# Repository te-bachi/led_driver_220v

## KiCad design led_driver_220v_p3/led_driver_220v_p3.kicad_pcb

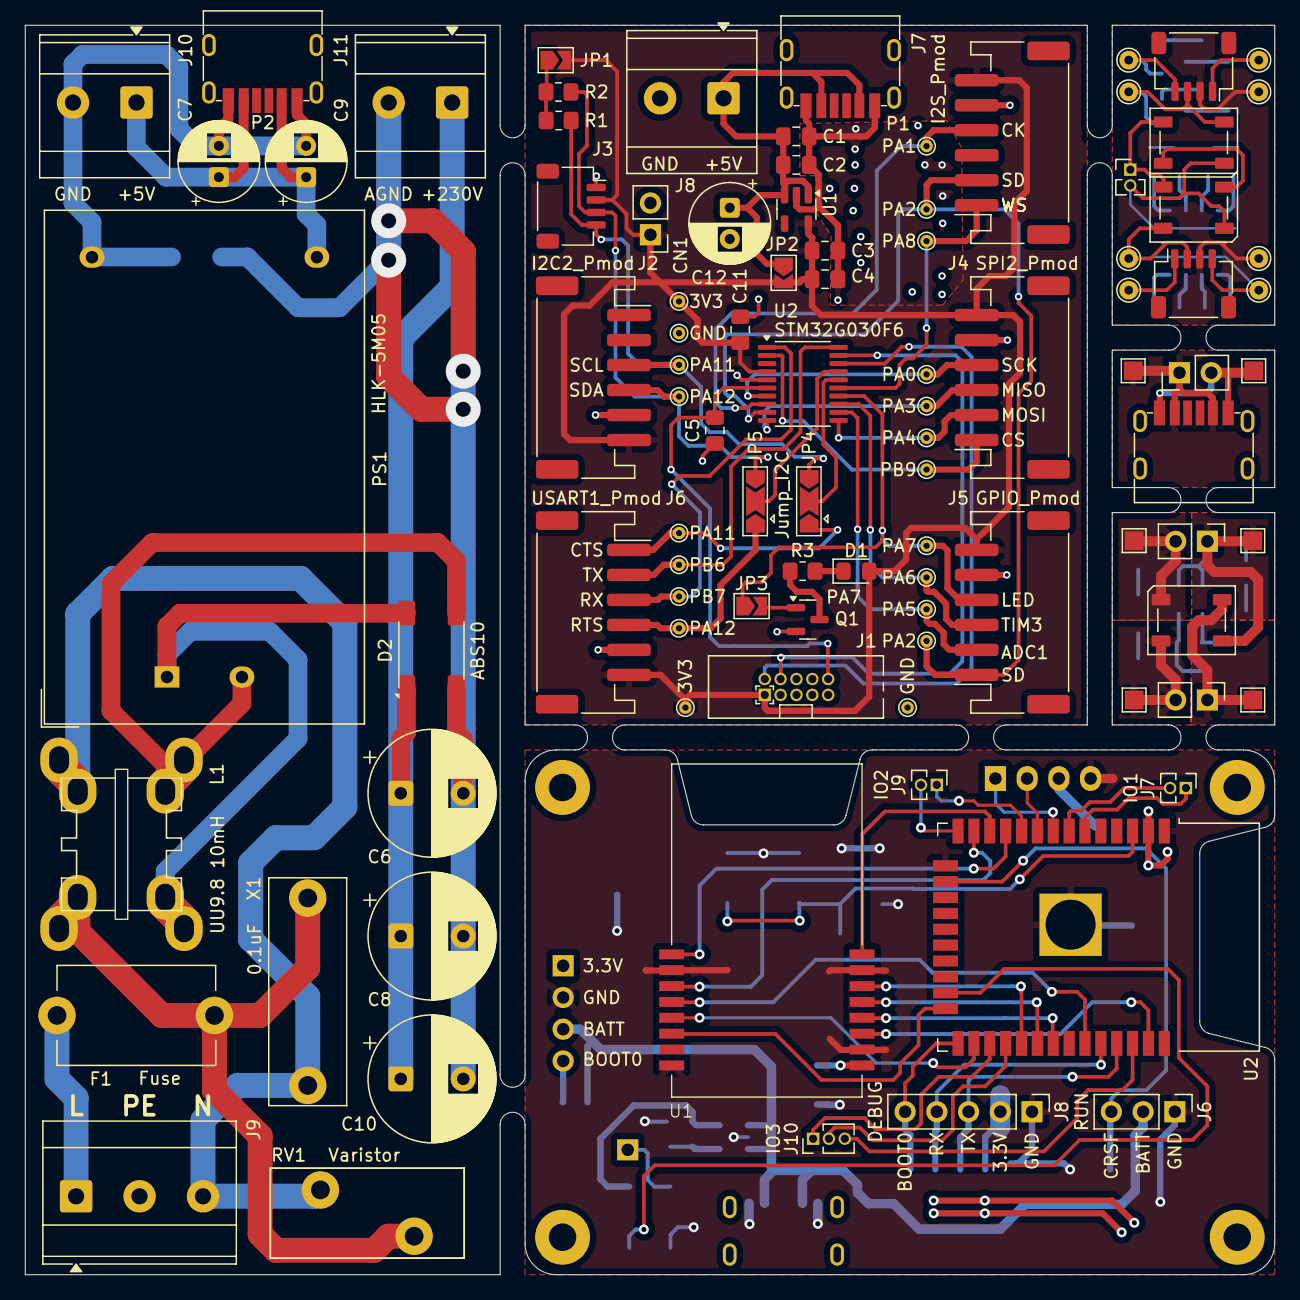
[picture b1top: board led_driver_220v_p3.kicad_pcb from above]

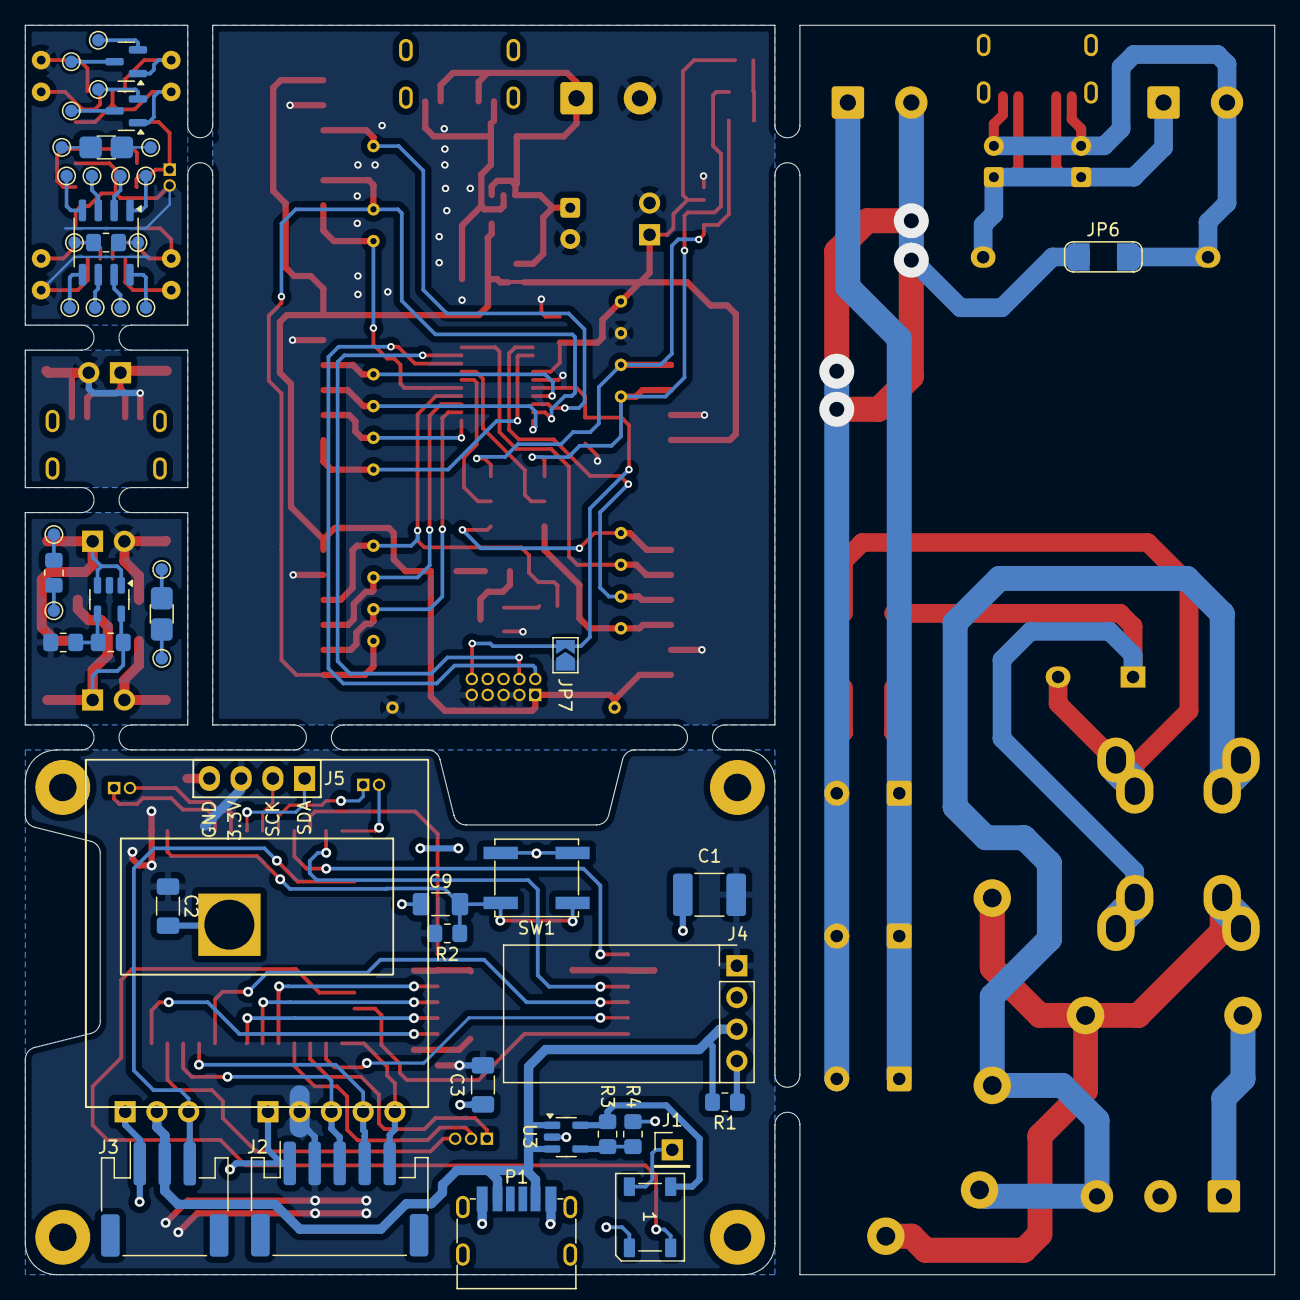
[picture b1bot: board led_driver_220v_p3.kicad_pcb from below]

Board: 2 copper layers, 100.0 x 100.0 mm, 149 parts (49 on the bottom side), 98 nets.

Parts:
C1, C4: 10uF; C_0805_2012Metric_Pad1.18x1.45mm_HandSolder
C1#2: 10uF; C_1812_4532Metric_Pad1.57x3.40mm_HandSolder
C2, C3, C5, C11: 100nF; C_0805_2012Metric_Pad1.18x1.45mm_HandSolder
C2#2, C3#2, C9#2: 10uF; C_1206_3216Metric_Pad1.33x1.80mm_HandSolder
C6, C8, C10: 6.8uF; CP_Radial_D10.0mm_P5.00mm
C7, C9, C12: 220uF; CP_Radial_D6.3mm_P2.50mm
CN1: 3.3V; PinHeader_1x02_P2.54mm_Vertical
D1: LED; LED_0805_2012Metric_Pad1.15x1.40mm_HandSolder
D1#2, D3, D4, D5: WS2812B; LED_WS2812B_PLCC4_5.0x5.0mm_P3.2mm
D2: ABS10; Diode_Bridge_Diotec_ABS
F1: Fuse; Fuse_Cylinder_3.6x10mm_Horizontal
H1, H2, H3, H4: MountingHole; MountingHole_2.2mm_M2_Pad
J1: SWD; SWD_2x05_P1.27mm
J1#2: LED Chain; PinHeader_1x01_P2.54mm_Vertical
J2: I2C2_Pmod; JST_PH_S6B-PH-SM4-TB_1x06-1MP_P2.00mm_Horizontal
J2#2: DEBUG; JST_PH_S5B-PH-SM4-TB_1x05-1MP_P2.00mm_Horizontal
J3: I2C2_Qwiic; JST_SH_SM04B-SRSS-TB_1x04-1MP_P1.00mm_Horizontal
J3#2: RUN; JST_PH_S3B-PH-SM4-TB_1x03-1MP_P2.00mm_Horizontal
J4: SPI2_Pmod; JST_PH_S6B-PH-SM4-TB_1x06-1MP_P2.00mm_Horizontal
J4#2: DC_DC; DC_DC_20x11
J5: GPIO_Pmod; JST_PH_S6B-PH-SM4-TB_1x06-1MP_P2.00mm_Horizontal
J5#2: OLED_I2C; OLED_27.3x27.8mm_no_holes
J6: USART1_Pmod; JST_PH_S6B-PH-SM4-TB_1x06-1MP_P2.00mm_Horizontal
J6#2: RUN; PinHeader_1x03_P2.54mm_Vertical
J7: I2S_Pmod; JST_PH_S6B-PH-SM4-TB_1x06-1MP_P2.00mm_Horizontal
J7#2: IO1; PinHeader_1x02_P1.27mm_Vertical
J8: Input_5V; TerminalBlock_Phoenix_MKDS-3-2-5.08_1x02_P5.08mm_Horizontal
J8#2: DEBUG; PinHeader_1x05_P2.54mm_Vertical
J9: AC-Input-230V; TerminalBlock_Phoenix_MKDS-3-3-5.08_1x03_P5.08mm_Horizontal
J9#2: IO2; PinHeader_1x02_P1.27mm_Vertical
J10: IO3; PinHeader_1x03_P1.27mm_Vertical
J10#2: DC-Output-5V; TerminalBlock_Phoenix_MKDS-3-2-5.08_1x02_P5.08mm_Horizontal
J11: DC-Output-230V; TerminalBlock_Phoenix_MKDS-3-2-5.08_1x02_P5.08mm_Horizontal
J12, J14: V; PinHeader_1x02_P2.54mm_Vertical
J13: D; PinHeader_1x02_P2.54mm_Vertical
J15: Qwiic_IN; JST_SH_SM04B-SRSS-TB_1x04-1MP_P1.00mm_Horizontal
J16: Qwiic_Out; JST_SH_SM04B-SRSS-TB_1x04-1MP_P1.00mm_Horizontal
J17: 5.0V; PinHeader_1x02_P1.27mm_Vertical
J51: SOIC-8; SO-8_3.9x4.9mm_P1.27mm
JP1: Jump_I2C2; SolderJumper-2_P1.3mm_Open_TrianglePad1.0x1.5mm
JP2: Jump_LDO; SolderJumper-2_P1.3mm_Open_TrianglePad1.0x1.5mm
JP3: Jump_LED; SolderJumper-2_P1.3mm_Open_TrianglePad1.0x1.5mm
JP4, JP5: Jump_I2C; SolderJumper-3_P2.0mm_Open_TrianglePad1.0x1.5mm
JP6: Jump-; SolderJumper-2
JP7: Jump_NRST; SolderJumper-2_P1.3mm_Open_TrianglePad1.0x1.5mm
L1: UU9.8 10mH; L_CommonMode_UU9.8_UU10.5
P1, P1#2, P2, P3: USB_C_Plug_USB2.0; USB_C_DEALON_009
PS1: HLK-5M05; Converter_ACDC_Hi-Link_HLK-5Mxx
Q1, Q2, Q3: BSS138; SOT-23
R1, R2: 2.2k; R_0805_2012Metric_Pad1.20x1.40mm_HandSolder
R1#2, R2#2: 10k; R_0805_2012Metric_Pad1.20x1.40mm_HandSolder
R3, R5, R9: R; R_0805_2012Metric_Pad1.20x1.40mm_HandSolder
R3#2, R6: 56k; R_0805_2012Metric_Pad1.20x1.40mm_HandSolder
R4, R7: 22k; R_0805_2012Metric_Pad1.20x1.40mm_HandSolder
R4#2, R8: R; R_1206_3216Metric_Pad1.30x1.75mm_HandSolder
RV1: Varistor; RV_Disc_D15.5mm_W7.2mm_P7.5mm
SW1: RESET; SW_SPST_EVQP0
TP1: PA0; TestPoint_THTPad_D1.0mm_Drill0.5mm_narrow
TP2: PA1; TestPoint_THTPad_D1.0mm_Drill0.5mm_narrow
TP3: PA3; TestPoint_THTPad_D1.0mm_Drill0.5mm_narrow
TP3a1, TP3b1: PA2; TestPoint_THTPad_D1.0mm_Drill0.5mm_narrow
TP4: PA4; TestPoint_THTPad_D1.0mm_Drill0.5mm_narrow
TP5: PA5; TestPoint_THTPad_D1.0mm_Drill0.5mm_narrow
TP6: PA6; TestPoint_THTPad_D1.0mm_Drill0.5mm_narrow
TP7: PA7; TestPoint_THTPad_D1.0mm_Drill0.5mm_narrow
TP8: PA8; TestPoint_THTPad_D1.0mm_Drill0.5mm_narrow
TP9: PB6; TestPoint_THTPad_D1.0mm_Drill0.5mm_narrow
TP9a1, TP9b1: PA11; TestPoint_THTPad_D1.0mm_Drill0.5mm_narrow
TP10: PB7; TestPoint_THTPad_D1.0mm_Drill0.5mm_narrow
TP10a1, TP10b1: PA12; TestPoint_THTPad_D1.0mm_Drill0.5mm_narrow
TP11: PB9; TestPoint_THTPad_D1.0mm_Drill0.5mm_narrow
TP12, TP13: 3V3; TestPoint_THTPad_D1.0mm_Drill0.5mm_narrow
TP14, TP15: GND; TestPoint_THTPad_D1.0mm_Drill0.5mm_narrow
TP16, TP18, TP20: USB+5V; TestPoint_Pad_1.5x1.5mm
TP17, TP19, TP21: USB-GND; TestPoint_Pad_1.5x1.5mm
TP22, TP23, TP24, TP25, TP26, TP27, TP28, TP29: TestPoint_THTPad_D1.5mm_Drill0.7mm
TP30, TP31, TP32, TP33, TP34, TP35, TP36, TP37, TP38, TP39, TP40, TP41, TP42, TP43, TP44, TP45, TP46, TP47, TP48, TP49: TestPoint_Pad_D1.0mm
U1: E28-2G4M27S-MY; E28-2G4M27S
U1#2: TLV75533PDBV; SOT-23-5
U2: STM32G030F6; TSSOP-20_4.4x6.5mm_P0.65mm
U2#2: ESP32-WROOM-32-MY; ESP32-WROOM-32_zhaw
U3, U3#2: SPX3819M5-L; SOT-23-5
X1: 0.1uF; C_Rect_L18.0mm_W6.0mm_P15.00mm_FKS3_FKP3

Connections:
+3.3V: C1#2.1, C2#2.1, C3.2, C3#2.1, C4.2, C11.2, CN1.1, D1.2 (A), J1.1, J2.6, J2#2.2, J3.2, J4.6, J4#2.1, J5.6, J5#2.2, J6.6, J7.6, J8#2.2, JP1.2 (B), JP2.2 (B), R2#2.2, TP12.1, TP13.1, U1.1 (VCC), U1#2.5 (OUT), U2.4 (VDD/VDDA), U2#2.2 (VDD)
+5V: C1.2, C2.2, C12.1, D1#2.1 (VDD), D3.1 (VDD), J8.1, J14.1, JP2.1 (A), P1.A9 (VBUS), P1.B9 (VBUS), R3#2.1, TP18.1, U1#2.1 (IN), U1#2.3 (EN), U3.1 (IN), U3.3 (EN), U3#2.5 (OUT)
+BATT: J3#2.2, J4#2.3, J6#2.2, P1#2.A9 (VBUS), P1#2.B9 (VBUS), R1#2.2, U3#2.1 (IN), U3#2.3 (EN)
/Addition/IN: D3.4 (DIN), J13.2, TP21.1
/Addition/OUT: D3.2 (DOUT), J13.1, R6.1, TP20.1, U3.5 (OUT)
/Addition/Q_3.3V: J15.2, J16.3, TP24.1, TP28.1
/Addition/Q_5.0V: D4.1 (VDD), D5.1 (VDD), J17.1
/Addition/Q_GND: D4.3 (VSS), D5.3 (VSS), J15.1, J16.4, J17.2, TP25.1, TP29.1
/Addition/Q_SCL_IN: J15.4, Q2.1 (G), TP22.1
/Addition/Q_SCL_OUT: J16.1, TP26.1
/Addition/Q_SDA_IN: D4.4 (DIN), J15.3, Q3.1 (G), TP23.1
/Addition/Q_SDA_OUT: D5.2 (DOUT), J16.2, TP27.1
/Addition/USB+5V: J12.1, P3.A9 (VBUS), P3.B9 (VBUS), TP16.1
/Addition/USB-GND: J12.2, P3.A12 (GND), P3.B12 (GND), TP17.1
/CRSF_RX_TX: J3#2.3, J6#2.3, U2#2.16 (IO13)
/E28_BUSY: U1.12 (BUSY), U2#2.33 (IO21)
/E28_DIO1: U1.13 (DIO1), U2#2.26 (IO4)
/E28_DIO2: U1.14 (DIO2), U2#2.24 (IO2)
/E28_MISO_RX: U1.4 (MOSI_RX), U2#2.31 (IO19)
/E28_MISO_TX: U1.3 (MISO_TX), U2#2.37 (IO23)
/E28_NRESET: U1.11 (NRESET), U2#2.13 (IO14)
/E28_NSS_CTS: U1.6 (NSS_CTS), U2#2.29 (IO5)
/E28_RX_EN: U1.8 (RX_EN), U2#2.12 (IO27)
/E28_SCK_RTS: U1.5 (SCK_RTS), U2#2.30 (IO18)
/E28_TX_EN: U1.9 (TX_EN), U2#2.11 (IO26)
/EN: C9#2.1, R2#2.1, SW1.2, U2#2.3 (EN)
/ESP32_BOOT0: J2#2.5, J8#2.5, U2#2.25 (IO0)
/ESP32_RX: J2#2.4, J8#2.4, U2#2.34 (RXD0/IO3)
/ESP32_TX: J2#2.3, J8#2.3, U2#2.35 (TXD0/IO1)
/High Voltage/DC+5V: C7.1, C9.1, J10#2.1, P2.A9 (VBUS), P2.B9 (VBUS), PS1.4 (+Vout)
/High Voltage/DC+230V: C6.1, C8.1, C10.1, D2.1 (+), J11.1
/High Voltage/DC-AGND: C6.2, C8.2, C10.2, D2.2 (-), J11.2, JP6.1 (A)
/High Voltage/DC-GND: C7.2, C9.2, J10#2.2, JP6.2 (B), P2.A12 (GND), P2.B12 (GND), PS1.3 (-Vout)
/High Voltage/L: F1.1, J9.1
/High Voltage/N: J9.3, L1.3, RV1.2, X1.2
/High Voltage/TIN_L: F1.2, L1.1, RV1.1, X1.1
/High Voltage/TOUT_L: D2.4, L1.2, PS1.1 (AC/L)
/High Voltage/TOUT_N: D2.3, L1.4, PS1.2 (AC/N)
/IO12: J9#2.2, U2#2.14 (IO12)
/IO16: J10.1, U2#2.27 (IO16)
/IO17: J10.2, U2#2.28 (IO17)
/IO22: J10.3, U2#2.36 (IO22)
/IO25: J9#2.1, U2#2.10 (IO25)
/IO34: J7#2.1, U2#2.6 (IO34)
/IO35: J7#2.2, U2#2.7 (IO35)
/LED_RGB: D1#2.4 (DIN), U2#2.23 (IO15)
/MCU/FETD: Q1.3 (D), R3.1
/MCU/FETG: JP3.2 (B), Q1.1 (G)
/MCU/GPIO_ADC1_IN5: J5.2, TP5.1, U2.12 (PA5)
/MCU/GPIO_PA7: J5.4, JP3.1 (A), TP7.1, U2.14 (PA7)
/MCU/GPIO_TIM3_CH1: J5.3, TP6.1, U2.13 (PA6)
/MCU/I2C2_SCL: J2.3, J3.4, JP4.3 (B), R1.2, TP9a1.1
/MCU/I2C2_SCL_UART1_CTS: JP4.2 (C), U2.16 (PA11_[PA9])
/MCU/I2C2_SDA: J2.4, J3.3, JP5.3 (B), R2.2, TP10a1.1
/MCU/I2C2_SDA_UART1_RTS: JP5.2 (C), U2.17 (PA12_[PA10])
/MCU/I2S1_CK: J7.4, TP2.1, U2.8 (PA1)
/MCU/I2S1_SD: J5.1, J7.2, TP3a1.1, TP3b1.1, U2.9 (PA2)
/MCU/I2S1_WS: J7.1, TP8.1, U2.15 (PB0/PB1/PB2/PA8)
/MCU/LED: D1.1 (K), R3.2
/MCU/NRST: C5.2, J1.10, JP7.2 (B), U2.6 (~RST/PF2)
/MCU/SPI2_CS: J4.1, TP11.1, U2.2 (PB9/PC14-OSC32_IN)
/MCU/SPI2_MISO: J4.3, TP3.1, U2.10 (PA3)
/MCU/SPI2_MOSI: J4.2, TP4.1, U2.11 (PA4)
/MCU/SPI2_SCK: J4.4, TP1.1, U2.7 (PA0)
/MCU/SWCLK: J1.4, U2.19 (PA15/PA14-BOOT0)
/MCU/SWDIO: J1.2, U2.18 (PA13)
/MCU/USART1_CTS: J6.1, JP4.1 (A), TP9b1.1
/MCU/USART1_RTS: J6.4, JP5.1 (A), TP10b1.1
/MCU/USART1_RX: J6.3, TP10.1, U2.1 (PB7/PB8)
/MCU/USART1_TX: J6.2, TP9.1, U2.20 (PB3/PB4/PB5/PB6)
/OLED_SCK: J5#2.3, U2#2.9 (IO33)
/OLED_SDA: J5#2.4, U2#2.8 (IO32)
GND: C1.1, C1#2.2, C2.1, C2#2.2, C3.1, C3#2.2, C4.1, C5.1, C9#2.2, C11.1, C12.2, CN1.2, D1#2.3 (VSS), D3.3 (VSS), J1.3, J1.5, J1.9, J2.5, J2#2.1, J3.1, J3#2.1, J4.5, J4#2.2, J5.5, J5#2.1, J6.5, J6#2.1, J7.5, J8.2, J8#2.1, J14.2, JP7.1 (A), P1.A12 (GND), P1.B12 (GND), P1#2.A12 (GND), P1#2.B12 (GND), Q1.2 (S), R4.2, R7.2, SW1.1, TP14.1, TP15.1, TP19.1, U1.2 (GND), U1.7 (GND), U1.10 (GND), U1.16 (GND), U1#2.2 (GND), U2.5 (VSS/VSSA), U2#2.1 (GND), U2#2.15 (GND), U2#2.38 (GND), U2#2.39 (GND), U3.2 (GND), U3#2.2 (GND)
unnamed: D1#2.2 (DOUT), J1#2.1
unnamed: D4.2 (DOUT), D5.4 (DIN)
unnamed: J4#2.4, R1#2.1
unnamed: J51.1, TP37.1
unnamed: J51.2, TP36.1
unnamed: J51.3, TP35.1
unnamed: J51.4, TP34.1
unnamed: J51.5, TP38.1
unnamed: J51.6, TP39.1
unnamed: J51.7, TP40.1
unnamed: J51.8, TP41.1
unnamed: JP1.1 (A), R1.1, R2.1
unnamed: Q2.3 (D), TP30.1
unnamed: Q2.2 (S), TP33.1
unnamed: Q3.3 (D), TP31.1
unnamed: Q3.2 (S), TP32.1
unnamed: R4#2.1, TP42.1
unnamed: R4#2.2, TP43.1
unnamed: R5.1, TP44.1
unnamed: R5.2, TP45.1
unnamed: R8.1, TP46.1
unnamed: R8.2, TP48.1
unnamed: R9.1, TP47.1
unnamed: R9.2, TP49.1
unnamed: R3#2.2, R4.1, R6.2, R7.1, U3.4 (ADJ), U3#2.4 (ADJ)

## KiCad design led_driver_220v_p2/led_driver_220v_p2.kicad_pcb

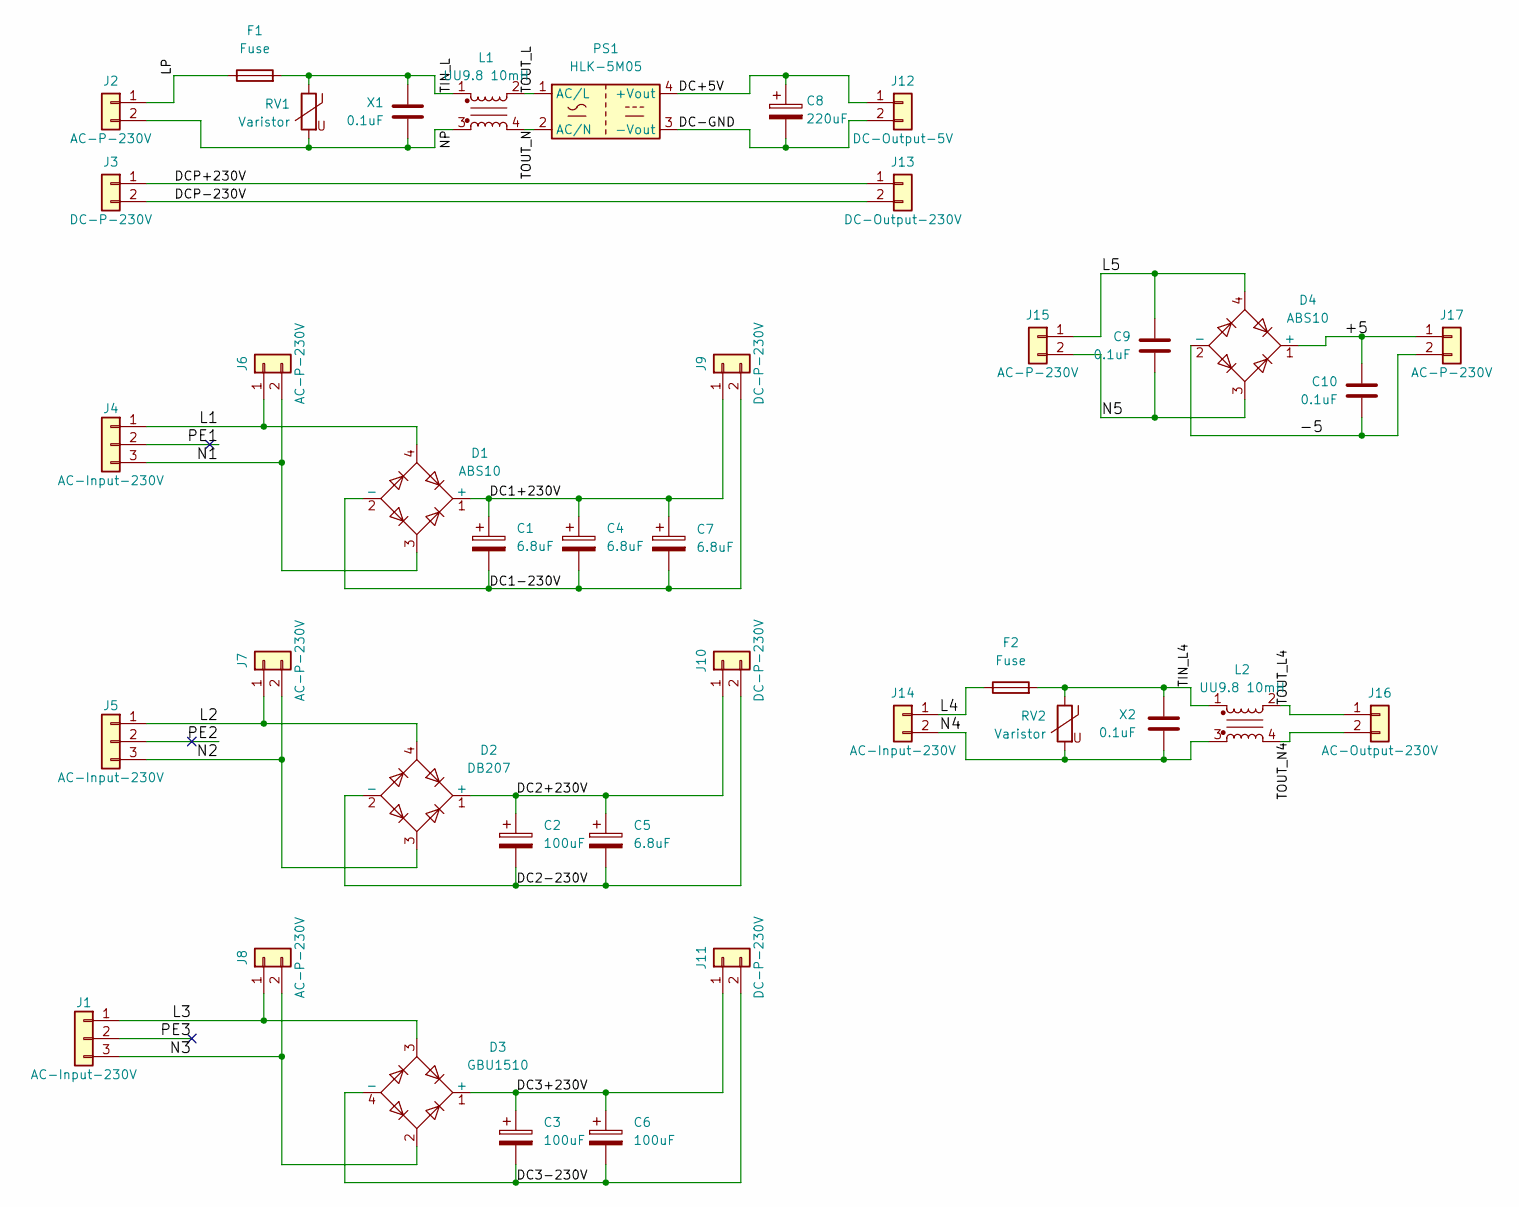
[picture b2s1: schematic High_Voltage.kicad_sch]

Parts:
C1, C4, C5, C7: 6.8uF; CP_Radial_D10.0mm_P5.00mm
C2, C3, C6: 100uF; CP_Radial_D18.0mm_P7.50mm
C8: 220uF; CP_Radial_D10.0mm_P5.00mm
C9, C10: 0.1uF; C_1812_4532Metric_Pad1.57x3.40mm_HandSolder
D1, D4: ABS10; Diode_Bridge_Diotec_ABS
D2: DB207; Diode_Bridge_DIP-4_W7.62mm_P5.08mm
D3: GBU1510; Diode_Bridge_Vishay_GBU
F1, F2: Fuse; Fuse_Cylinder_3.6x10mm_Horizontal
J1, J4, J5: AC-Input-230V; TerminalBlock_Phoenix_MKDS-3-3-5.08_1x03_P5.08mm_Horizontal
J2, J6, J7, J8, J15, J17: AC-P-230V; TerminalBlock_P5.08mm_Horizontal
J3, J9, J10, J11: DC-P-230V; TerminalBlock_P5.08mm_Horizontal
J12: DC-Output-5V; TerminalBlock_Phoenix_MKDS-3-2-5.08_1x02_P5.08mm_Horizontal
J13: DC-Output-230V; TerminalBlock_Phoenix_MKDS-3-2-5.08_1x02_P5.08mm_Horizontal
J14: AC-Input-230V; TerminalBlock_Phoenix_MKDS-3-2-5.08_1x02_P5.08mm_Horizontal
J16: AC-Output-230V; TerminalBlock_Phoenix_MKDS-3-2-5.08_1x02_P5.08mm_Horizontal
L1, L2: UU9.8 10mH; L_CommonMode_UU9.8_UU10.5
PS1: HLK-5M05; Converter_ACDC_Hi-Link_HLK-5Mxx
RV1, RV2: Varistor; RV_Disc_D15.5mm_W7.2mm_P7.5mm
X1, X2: 0.1uF; C_Rect_L18.0mm_W6.0mm_P15.00mm_FKS3_FKP3

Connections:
/High Voltage/+5: C10.1, D4.1 (+), J17.1
/High Voltage/-5: C10.2, D4.2 (-), J17.2
/High Voltage/DC1+230V: C1.1, C4.1, C7.1, D1.1 (+), J9.1
/High Voltage/DC1-230V: C1.2, C4.2, C7.2, D1.2 (-), J9.2
/High Voltage/DC2+230V: C2.1, C5.1, D2.1 (+), J10.1
/High Voltage/DC2-230V: C2.2, C5.2, D2.2 (-), J10.2
/High Voltage/DC3+230V: C3.1, C6.1, D3.1 (+), J11.1
/High Voltage/DC3-230V: C3.2, C6.2, D3.4 (-), J11.2
/High Voltage/DC+5V: C8.1, J12.1, PS1.4 (+Vout)
/High Voltage/DC-GND: C8.2, J12.2, PS1.3 (-Vout)
/High Voltage/DCP+230V: J3.1, J13.1
/High Voltage/DCP-230V: J3.2, J13.2
/High Voltage/L1: D1.4, J4.1, J6.1
/High Voltage/L2: D2.4, J5.1, J7.1
/High Voltage/L3: D3.3, J1.1, J8.1
/High Voltage/L4: F2.1, J14.1
/High Voltage/L5: C9.1, D4.4, J15.1
/High Voltage/LP: F1.1, J2.1
/High Voltage/N1: D1.3, J4.3, J6.2
/High Voltage/N2: D2.3, J5.3, J7.2
/High Voltage/N3: D3.2, J1.3, J8.2
/High Voltage/N4: J14.2, L2.3, RV2.2, X2.2
/High Voltage/N5: C9.2, D4.3, J15.2
/High Voltage/NP: J2.2, L1.3, RV1.2, X1.2
/High Voltage/PE1: J4.2
/High Voltage/PE2: J5.2
/High Voltage/PE3: J1.2
/High Voltage/TIN_L: F1.2, L1.1, RV1.1, X1.1
/High Voltage/TIN_L4: F2.2, L2.1, RV2.1, X2.1
/High Voltage/TOUT_L: L1.2, PS1.1 (AC/L)
/High Voltage/TOUT_L4: J16.1, L2.2
/High Voltage/TOUT_N: L1.4, PS1.2 (AC/N)
/High Voltage/TOUT_N4: J16.2, L2.4

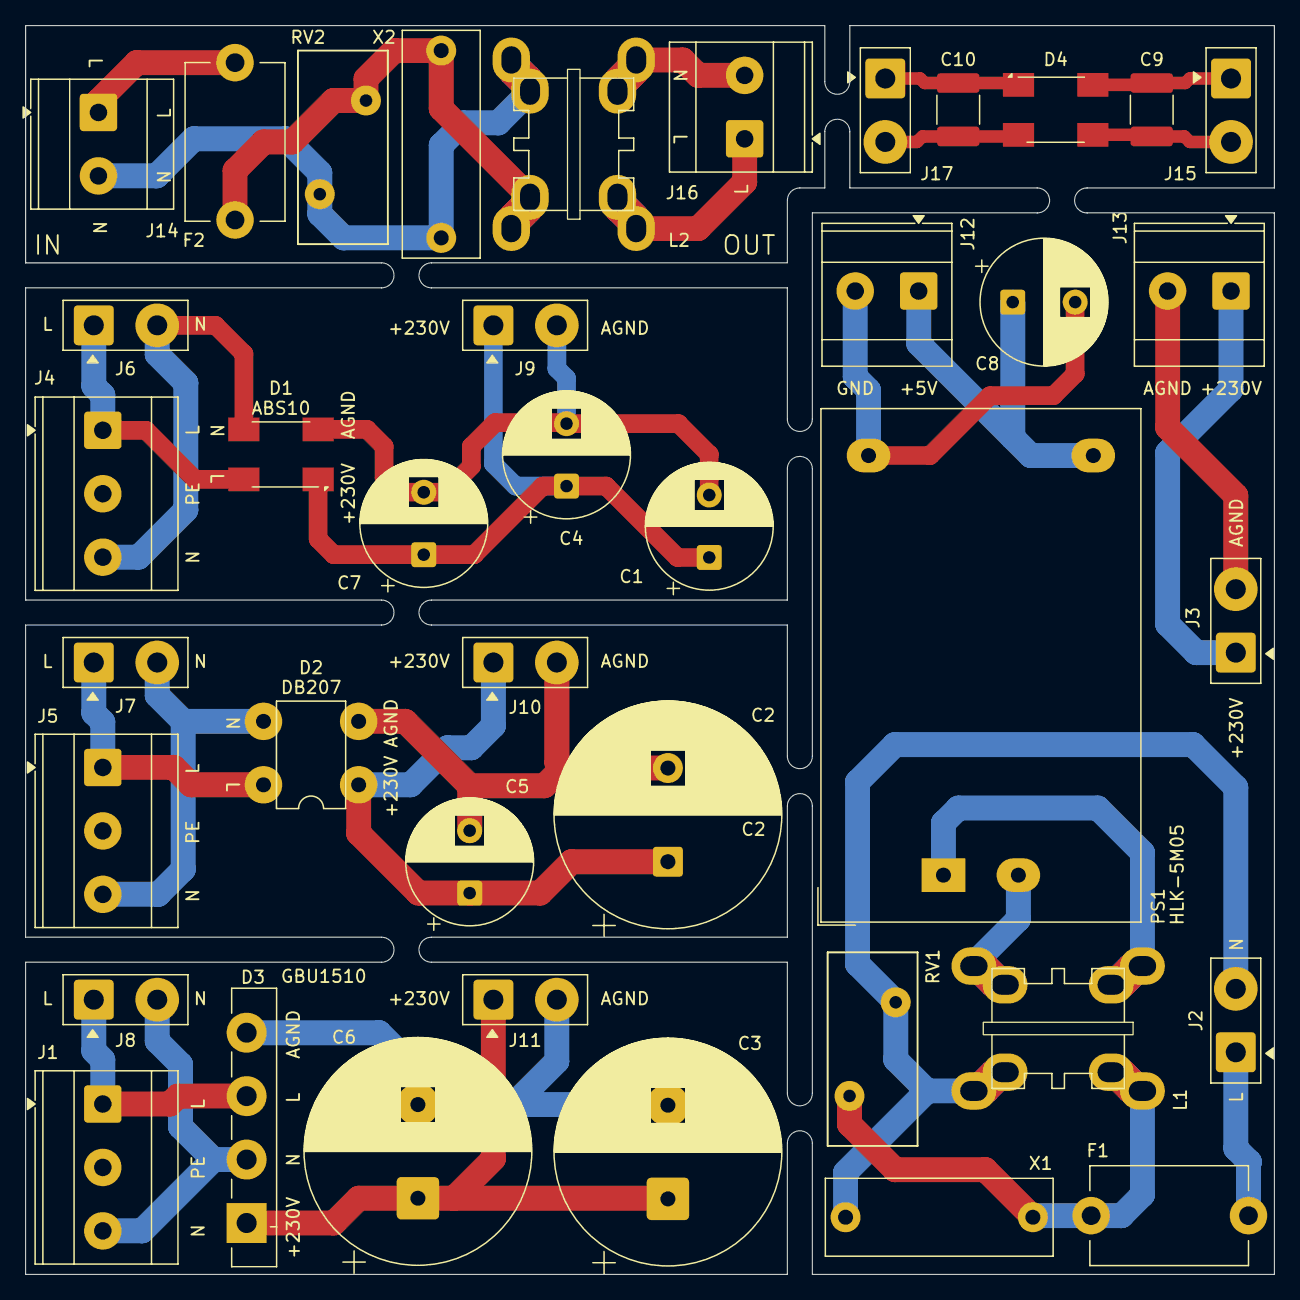
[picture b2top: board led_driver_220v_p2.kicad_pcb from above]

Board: 2 copper layers, 100.0 x 100.0 mm, 40 parts (0 on the bottom side), 30 nets.

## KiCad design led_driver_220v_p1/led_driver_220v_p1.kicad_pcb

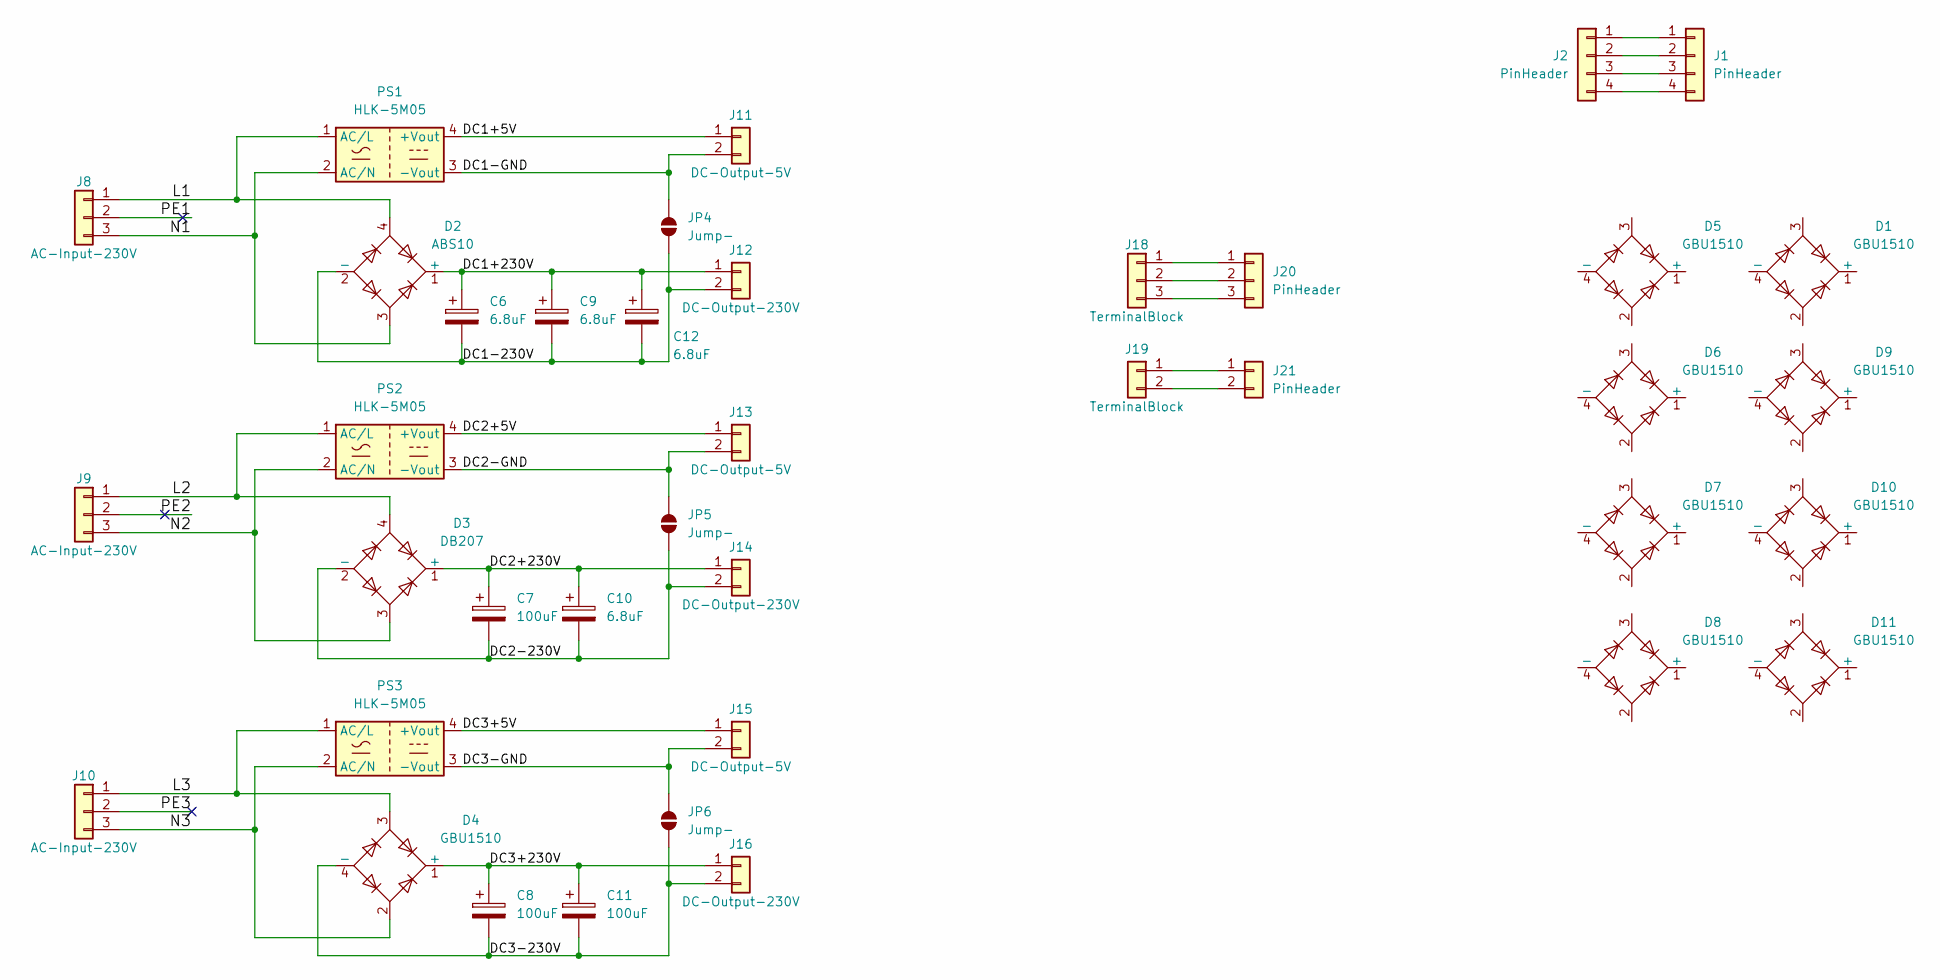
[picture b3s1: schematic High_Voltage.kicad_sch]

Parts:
C6, C9, C10, C12: 6.8uF; CP_Radial_D10.0mm_P5.00mm
C7, C8, C11: 100uF; CP_Radial_D18.0mm_P7.50mm
D1, D4, D5, D6, D7, D8, D9, D10, D11: GBU1510; Diode_Bridge_Vishay_GBU
D2: ABS10; Diode_Bridge_Diotec_ABS
D3: DB207; Diode_Bridge_DIP-4_W7.62mm_P5.08mm
J1: PinHeader; Diode_Bridge_Vishay_GBU
J2: PinHeader; PinHeader_1x04_P2.54mm_Vertical
J8, J9, J10: AC-Input-230V; TerminalBlock_Phoenix_MKDS-3-3-5.08_1x03_P5.08mm_Horizontal
J11, J13, J15: DC-Output-5V; TerminalBlock_Phoenix_MKDS-3-2-5.08_1x02_P5.08mm_Horizontal
J12, J14, J16: DC-Output-230V; TerminalBlock_Phoenix_MKDS-3-2-5.08_1x02_P5.08mm_Horizontal
J18: TerminalBlock; TerminalBlock_Phoenix_MKDS-3-3-5.08_1x03_P5.08mm_Horizontal
J19: TerminalBlock; TerminalBlock_Phoenix_MKDS-3-2-5.08_1x02_P5.08mm_Horizontal
J20: PinHeader; PinHeader_1x03_P2.54mm_Vertical
J21: PinHeader; PinHeader_1x02_P2.54mm_Vertical
JP4, JP5, JP6: Jump-; SolderJumper-2
PS1, PS2, PS3: HLK-5M05; Converter_ACDC_Hi-Link_HLK-5Mxx

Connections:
/High Voltage/DC1+5V: J11.1, PS1.4 (+Vout)
/High Voltage/DC1+230V: C6.1, C9.1, C12.1, D2.1 (+), J12.1
/High Voltage/DC1-230V: C6.2, C9.2, C12.2, D2.2 (-), J12.2, JP4.1 (A)
/High Voltage/DC1-GND: J11.2, JP4.2 (B), PS1.3 (-Vout)
/High Voltage/DC2+5V: J13.1, PS2.4 (+Vout)
/High Voltage/DC2+230V: C7.1, C10.1, D3.1 (+), J14.1
/High Voltage/DC2-230V: C7.2, C10.2, D3.2 (-), J14.2, JP5.1 (A)
/High Voltage/DC2-GND: J13.2, JP5.2 (B), PS2.3 (-Vout)
/High Voltage/DC3+5V: J15.1, PS3.4 (+Vout)
/High Voltage/DC3+230V: C8.1, C11.1, D4.1 (+), J16.1
/High Voltage/DC3-230V: C8.2, C11.2, D4.4 (-), J16.2, JP6.1 (A)
/High Voltage/DC3-GND: J15.2, JP6.2 (B), PS3.3 (-Vout)
/High Voltage/L1: D2.4, J8.1, PS1.1 (AC/L)
/High Voltage/L2: D3.4, J9.1, PS2.1 (AC/L)
/High Voltage/L3: D4.3, J10.1, PS3.1 (AC/L)
/High Voltage/N1: D2.3, J8.3, PS1.2 (AC/N)
/High Voltage/N2: D3.3, J9.3, PS2.2 (AC/N)
/High Voltage/N3: D4.2, J10.3, PS3.2 (AC/N)
/High Voltage/PE1: J8.2
/High Voltage/PE2: J9.2
/High Voltage/PE3: J10.2
unnamed: J1.1, J2.1
unnamed: J1.2, J2.2
unnamed: J1.3, J2.3
unnamed: J1.4, J2.4
unnamed: J18.1, J20.1
unnamed: J18.2, J20.2
unnamed: J18.3, J20.3
unnamed: J19.1, J21.1
unnamed: J19.2, J21.2

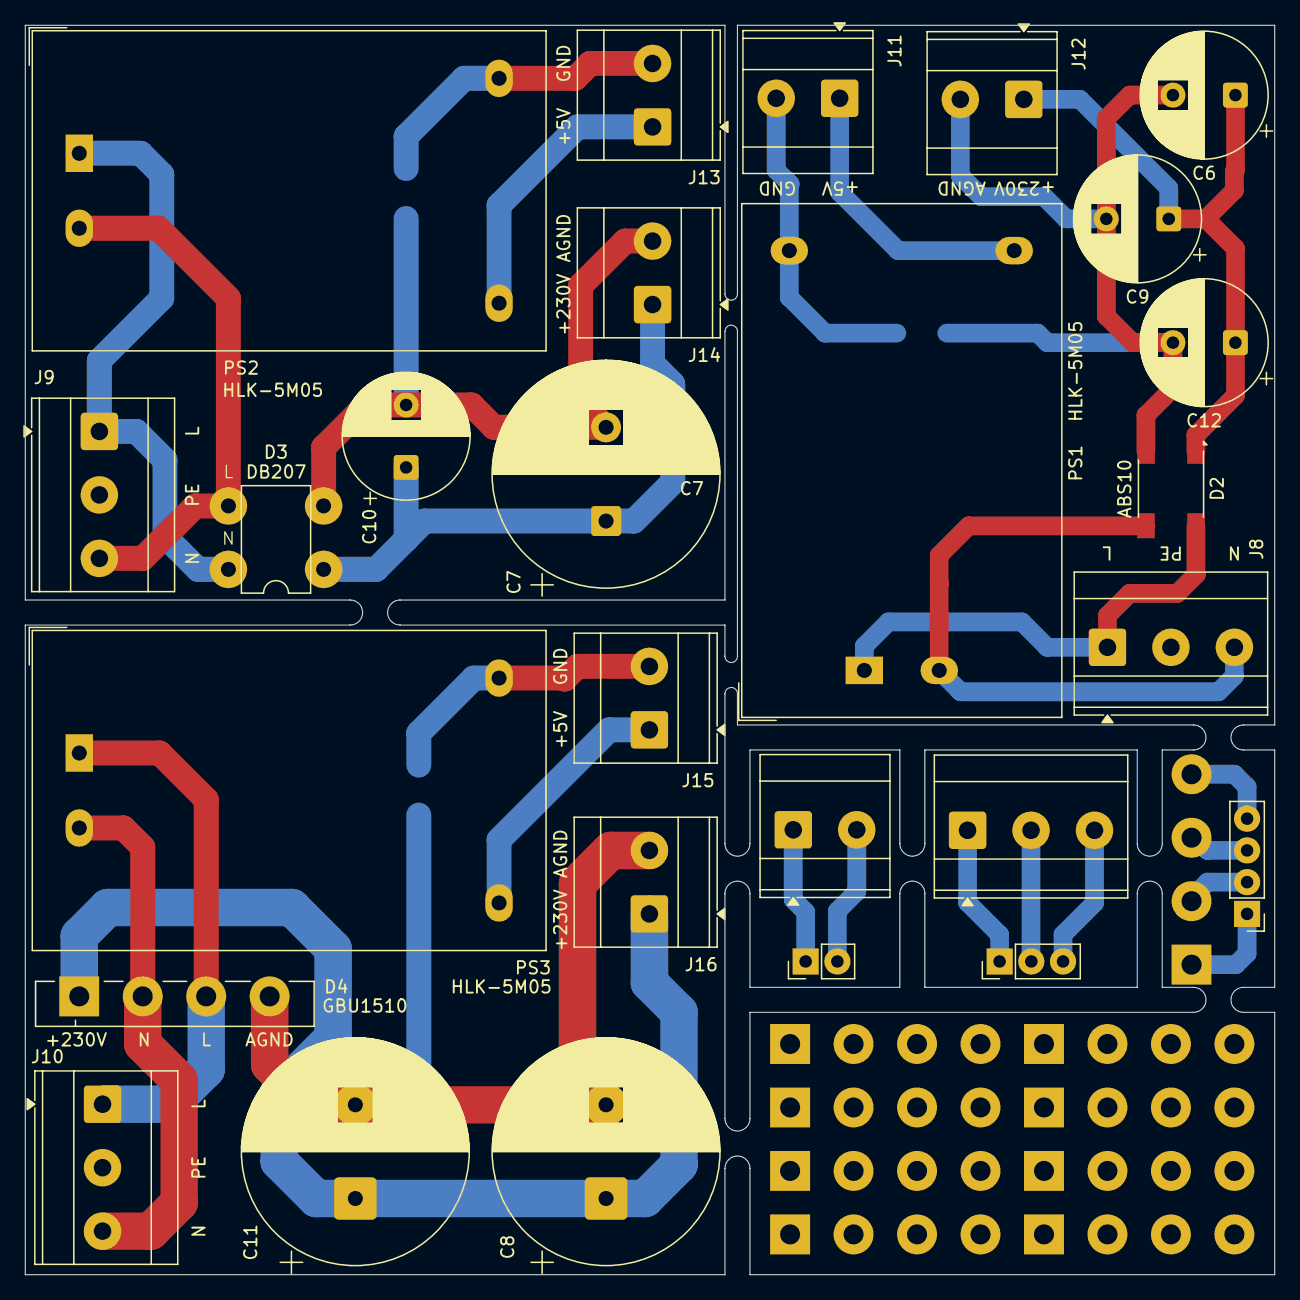
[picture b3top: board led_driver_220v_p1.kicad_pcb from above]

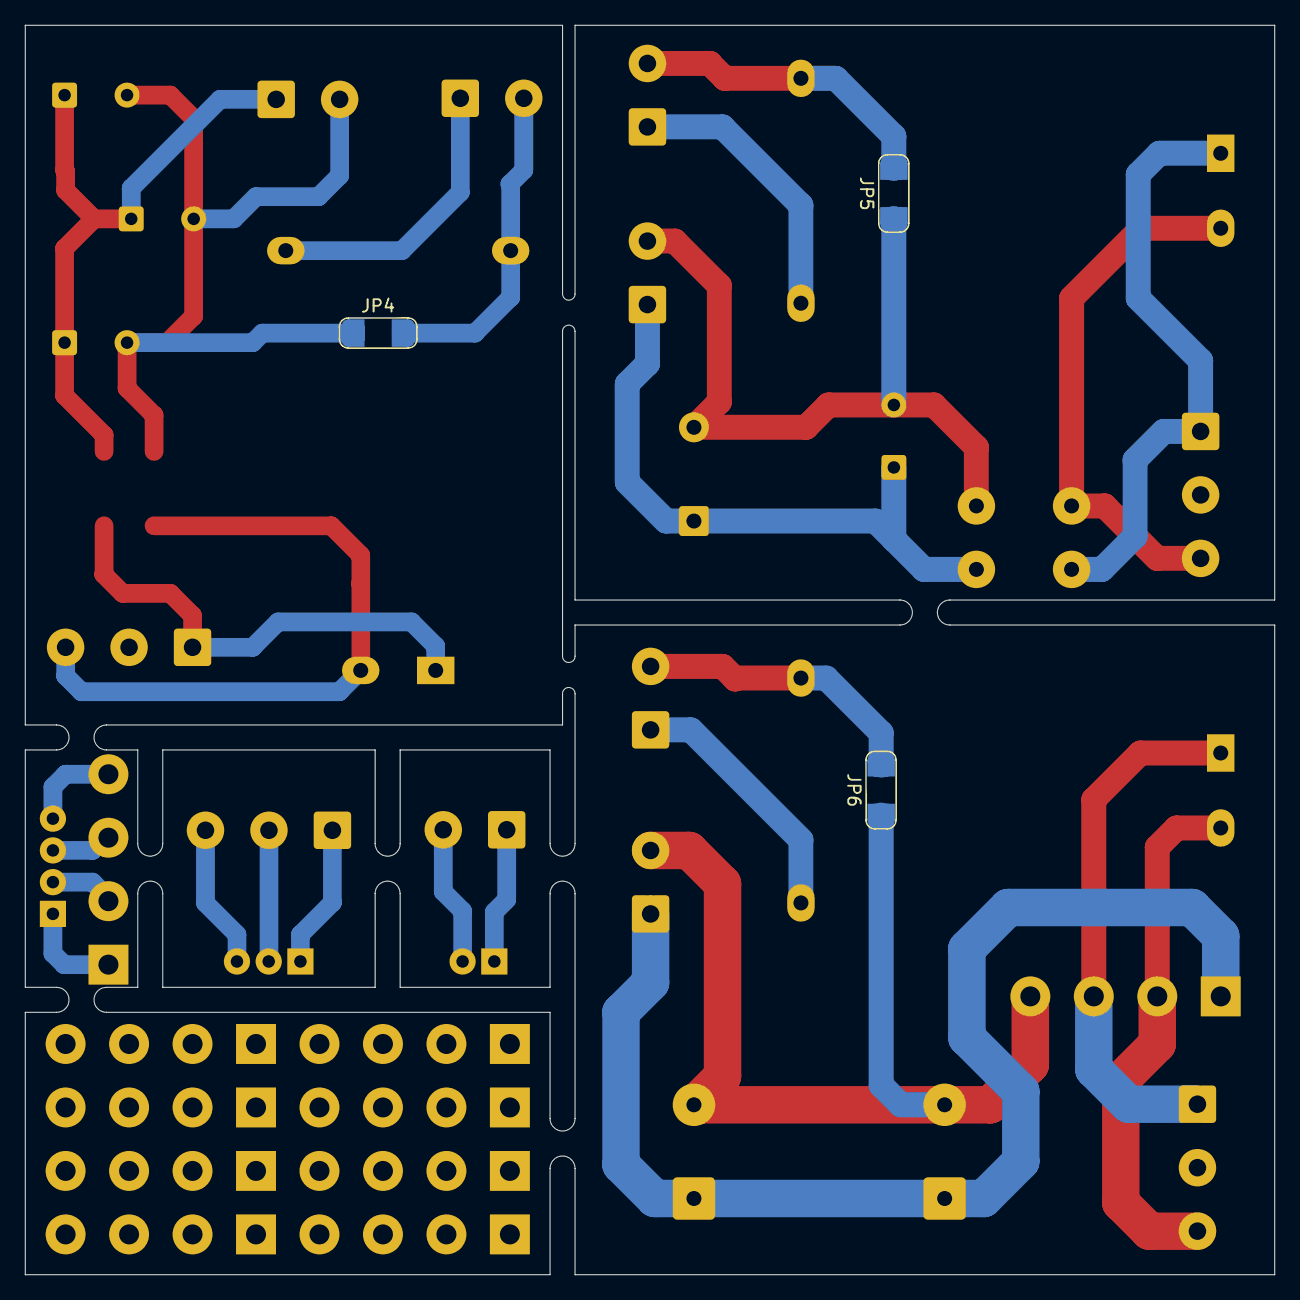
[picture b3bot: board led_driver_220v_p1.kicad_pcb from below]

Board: 2 copper layers, 100.0 x 100.0 mm, 39 parts (3 on the bottom side), 27 nets.

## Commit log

2025-06-26 led_driver_220v_p3 update
2025-06-27 led_driver_220v gerber
2025-06-27 led_driver_220v_p3 update + gerber
